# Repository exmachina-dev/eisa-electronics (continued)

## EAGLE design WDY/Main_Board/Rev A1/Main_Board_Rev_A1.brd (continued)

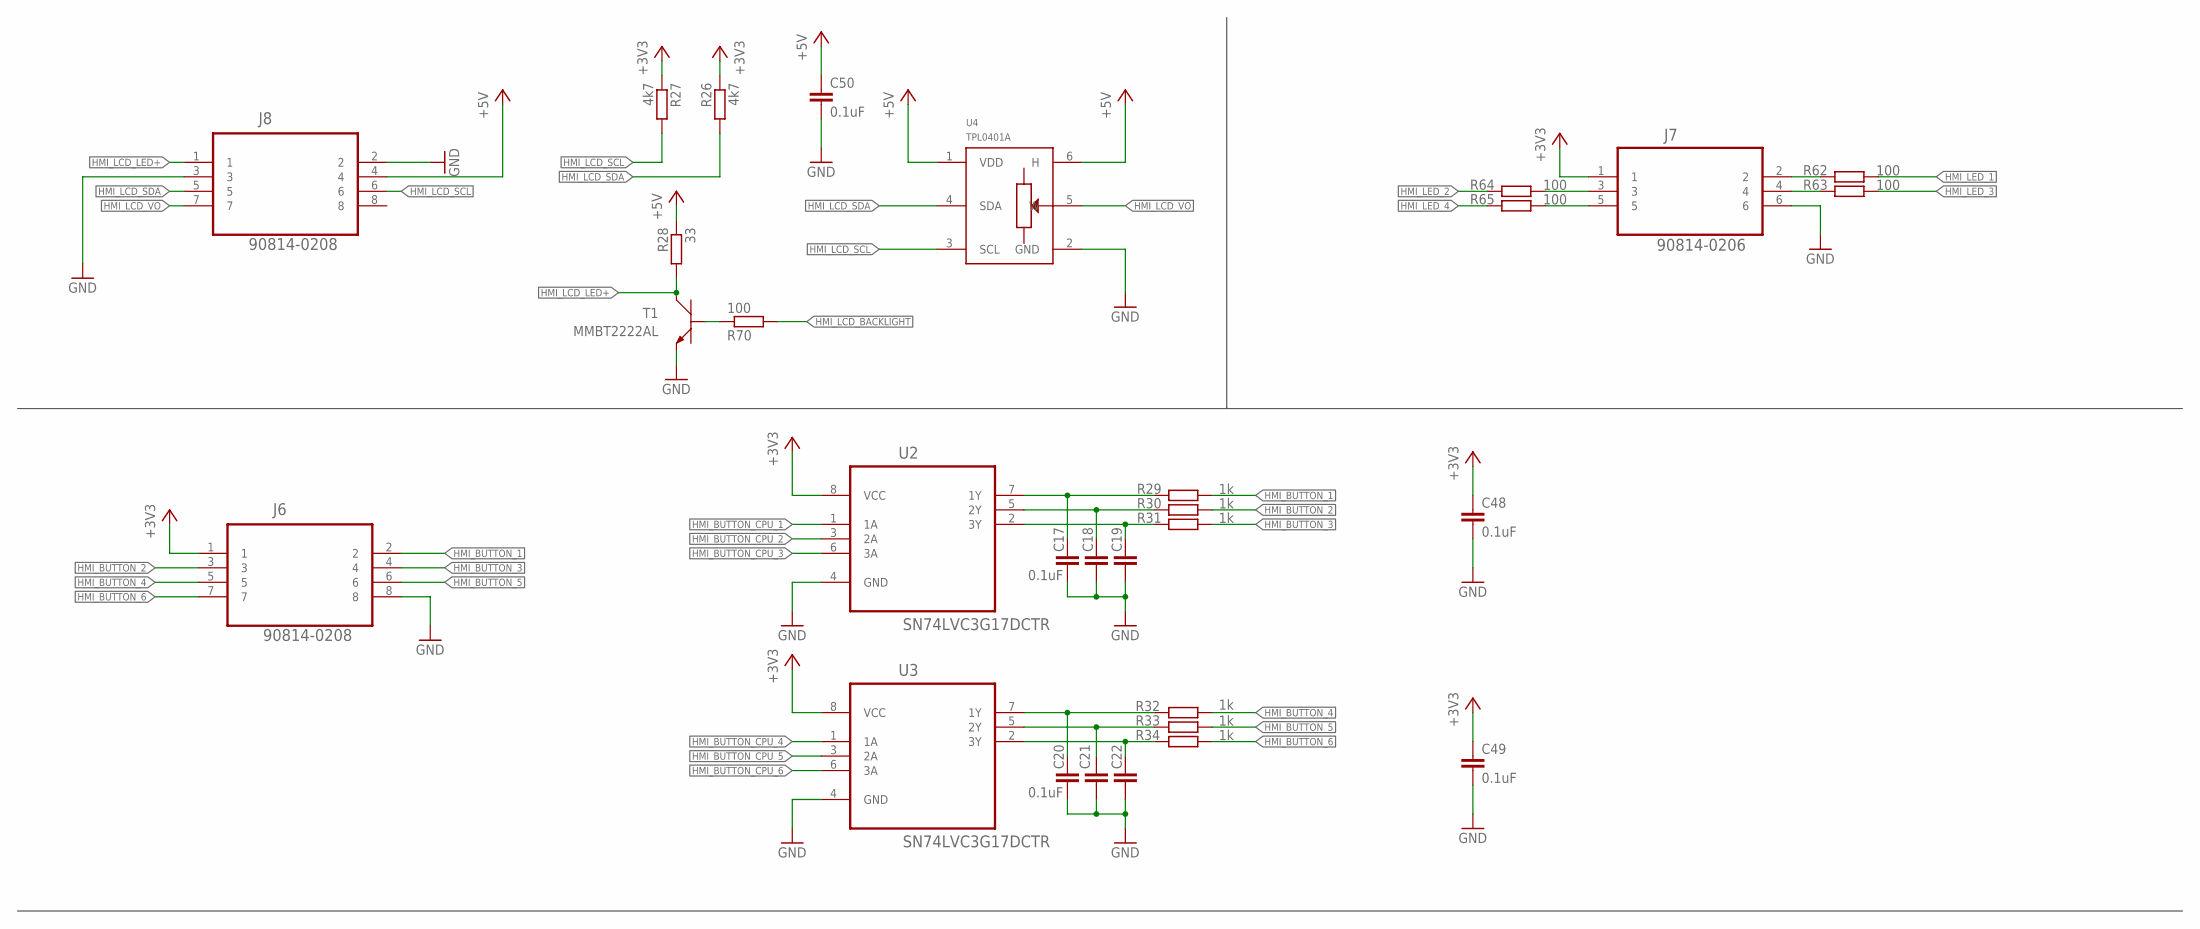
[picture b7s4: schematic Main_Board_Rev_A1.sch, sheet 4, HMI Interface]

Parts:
C17, C18, C19, C20, C21, C22, C48, C49, C50: 0.1uF; C0603
J6, J8: 90814-0208; MOLEX_90814-0208
J7: 90814-0206; MOLEX_90814-0206
R26, R27: 4k7; R0603
R28: 33; R0603
R29, R30, R31, R32, R33, R34: 1k; R0603
R62, R63, R64, R65, R70: 100; R0603
T1: MMBT2222AL; SOT−23
U2, U3: SN74LVC3G17DCTR; SOP65P400X130-8N
U4: TPL0401A; SC-70-DCK

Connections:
+3V3: C48.1, C49.1, J6.1, J7.1, R26.1, R27.1, U2.8 (VCC), U3.8 (VCC); also elsewhere on the board
+5V: C50.1, J8.4, R28.1, U4.1 (VDD), U4.6 (H); also elsewhere on the board
GND: C17.2, C18.2, C19.2, C20.2, C21.2, C22.2, C48.2, C49.2, C50.2, J6.8, J7.6, J8.2, J8.3, T1.2 (E), U2.4 (GND), U3.4 (GND), U4.2 (GND); also elsewhere on the board
HMI_BUTTON_1: J6.2, R29.1
HMI_BUTTON_2: J6.3, R30.1
HMI_BUTTON_3: J6.4, R31.1
HMI_BUTTON_4: J6.5, R32.1
HMI_BUTTON_5: J6.6, R33.1
HMI_BUTTON_6: J6.7, R34.1
HMI_BUTTON_CPU_1: U2.1 (1A); also elsewhere on the board
HMI_BUTTON_CPU_2: U2.3 (2A); also elsewhere on the board
HMI_BUTTON_CPU_3: U2.6 (3A); also elsewhere on the board
HMI_BUTTON_CPU_4: U3.1 (1A); also elsewhere on the board
HMI_BUTTON_CPU_5: U3.3 (2A); also elsewhere on the board
HMI_BUTTON_CPU_6: U3.6 (3A); also elsewhere on the board
HMI_LCD_BACKLIGHT: R70.2; also elsewhere on the board
HMI_LCD_LED+: J8.1, R28.2, T1.3 (C)
HMI_LCD_SCL: J8.6, R27.2, U4.3 (SCL); also elsewhere on the board
HMI_LCD_SDA: J8.5, R26.2, U4.4 (SDA); also elsewhere on the board
HMI_LCD_VO: J8.7, U4.5 (W)
HMI_LED_1: R62.1; also elsewhere on the board
HMI_LED_2: R64.2; also elsewhere on the board
HMI_LED_3: R63.1; also elsewhere on the board
HMI_LED_4: R65.2; also elsewhere on the board
unnamed: J7.3, R64.1
unnamed: J7.5, R65.1
unnamed: R70.1, T1.1 (B)
unnamed: C17.1, R29.2, U2.7 (1Y)
unnamed: C18.1, R30.2, U2.5 (2Y)
unnamed: C19.1, R31.2, U2.2 (3Y)
unnamed: C20.1, R32.2, U3.7 (1Y)
unnamed: C21.1, R33.2, U3.5 (2Y)
unnamed: C22.1, R34.2, U3.2 (3Y)
unnamed: J7.2, R62.2
unnamed: J7.4, R63.2

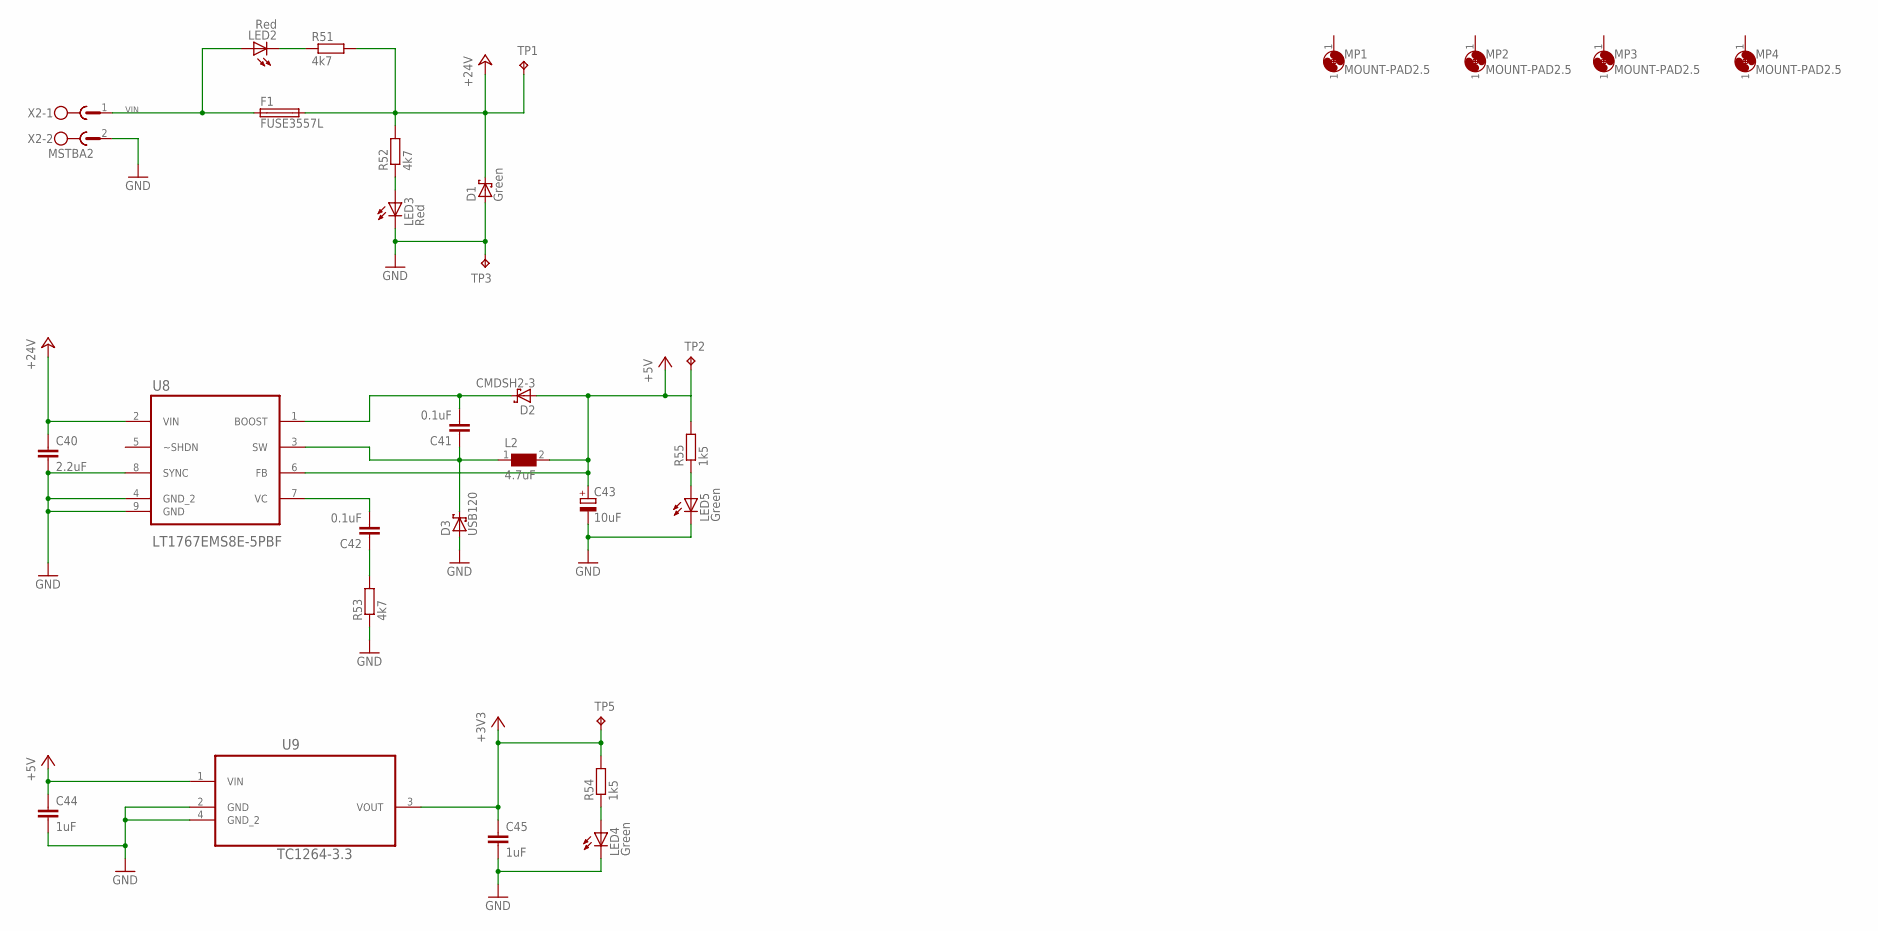
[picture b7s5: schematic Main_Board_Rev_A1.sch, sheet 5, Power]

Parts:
C40: 2.2uF; C0603
C41, C42: 0.1uF; C0603
C43: 10uF; CT3216
C44, C45: 1uF; C0603
D1: Green; SMB
D2: CMDSH2-3; SOD323-W
D3: USB120; DO216AA
F1: FUSE3557L; 3557-LITTLE
L2: 4.7uF; WE-PD_1030/1050
LED2, LED3: Red; CHIPLED_0603
LED4, LED5: Green; CHIP-LED0603; MPN OVS-0604
MP1, MP2, MP3, MP4: MOUNT-PAD2.5; P2.5
R51, R52, R53: 4k7; R0603
R54, R55: 1k5; R0603; MPN MCMR06X1501FTL
TP1, TP2, TP3, TP5: TPB1,27; B1,27
U8: LT1767EMS8E-5PBF; SOP65P490X110-9N
U9: TC1264-3.3; SOT230P700X180-4N
X2: MSTBA2

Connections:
+3V3: C45.1, R54.2, TP5.TP, U9.3 (VOUT); also elsewhere on the board
+5V: C43.+, C44.1, D2.A, L2.2, R55.2, TP2.TP, U8.6 (FB), U9.1 (VIN); also elsewhere on the board
+24V: C40.1, D1.C, F1.3 (2), F1.4 (2), R51.2, R52.2, TP1.TP, U8.2 (VIN); also elsewhere on the board
GND: C40.2, C43.-, C44.2, C45.2, D1.A, D3.A, LED3.C, LED4.C, LED5.C, R53.1, TP3.TP, U8.4 (GND_2), U8.8 (SYNC), U8.9 (GND), U9.2 (GND), U9.4 (GND_2), X2.2; also elsewhere on the board
unnamed: C41.2, D2.C, U8.1 (BOOST)
unnamed: LED3.A, R52.1
unnamed: LED2.C, R51.1
unnamed: C42.1, R53.2
unnamed: C42.2, U8.7 (VC)
unnamed: C41.1, D3.C, L2.1, U8.3 (SW)
unnamed: LED4.A, R54.1
unnamed: LED5.A, R55.1
VIN: F1.1, F1.2 (1), LED2.A, X2.1

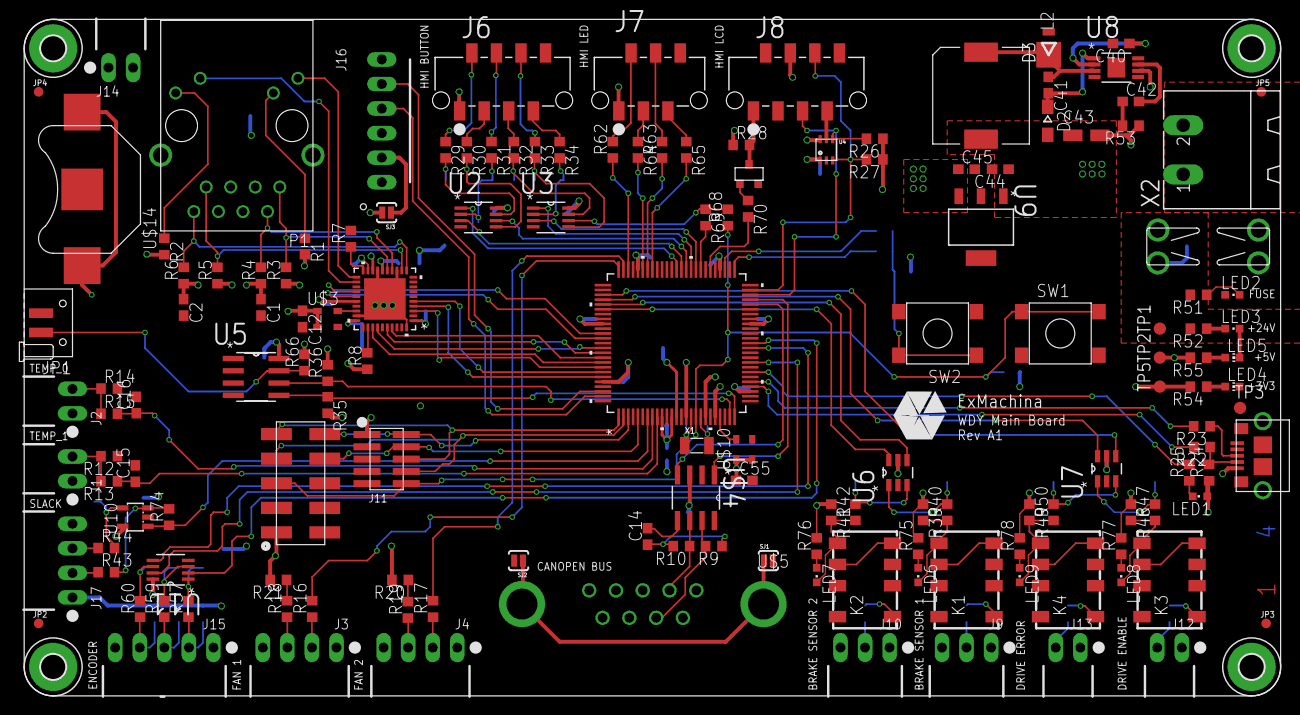
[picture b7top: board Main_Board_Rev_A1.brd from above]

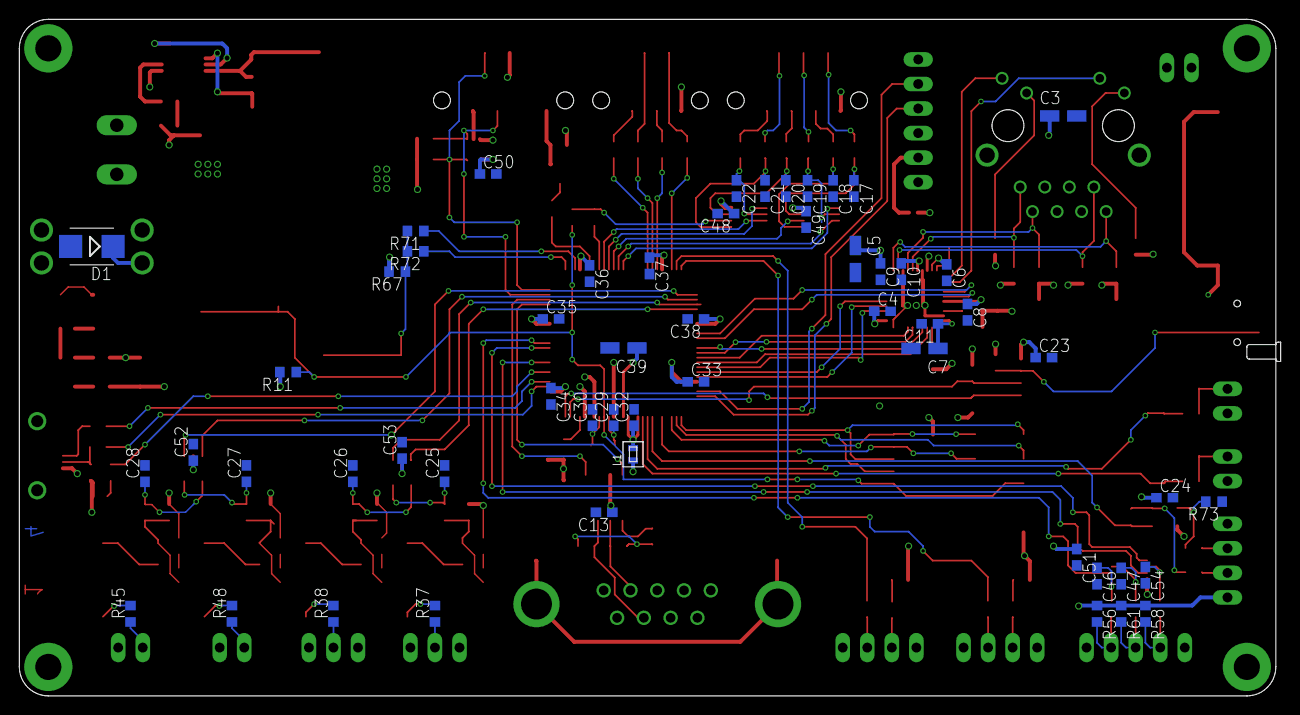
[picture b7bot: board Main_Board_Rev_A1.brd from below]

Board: 4 copper layers, 130.5 x 70.0 mm, 209 parts (55 on the bottom side), 154 nets.

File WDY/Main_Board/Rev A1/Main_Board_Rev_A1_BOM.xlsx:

|  |  | Project | WDY - Main Board
 |  |  | Author | AB
 |  |  | Date | 42709
 |  |  | Rev | A1
Qty | Value | Device | Package | Parts | Description
1 | Green | LEDCHIPLED_0603 | CHIPLED_0603 | LED1 | LED
1 |  | STPS3L40UF | SMB | D1
31 | 0.1uF | C-EUC0603 | C0603 | C17, C18, C19, C20, C21, C22, C23, C24, C25, C26, C27, C28, C32, C33, C34, C35,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 | CAPACITOR, European symbol
1 | 0603PS-103KLB | 0603PS | 603 | L1
4 | 0R | R-EU_R0603 | R0603 | R68, R69, R71, R72 | RESISTOR, European symbol
19 | 100 | R-EU_R0603 | R0603 | R17, R18, R19, R37, R38, R40, R42, R45, R47, R48, R50, R57, R59, R60, R62, R63,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 | RESISTOR, European symbol
10 | 100nF | C-EUC0603 | C0603 | C1, C2, C4, C6, C8, C9, C10, C11, C12, C13 | CAPACITOR, European symbol
2 | 10K | R-EU_R0603 | R0603 | R11, R67 | RESISTOR, European symbol
6 | 10k | R-EU_R0603 | R0603 | R12, R13, R14, R15, R20, R21 | RESISTOR, European symbol
4 | 10uF | CPOL-EUCT3216 | CT3216 | C5, C7, C39, C43 | POLARIZED CAPACITOR, European symbol
1 | 1241050-5 | 1241050-5 | 2.54/2X5 | J5
2 | 18pF | C-EUC0603 | C0603 | C29, C30 | CAPACITOR, European symbol
1 | 1K | R-EU_R0603 | R0603 | R16 | RESISTOR, European symbol
6 | 1k | R-EU_R0603 | R0603 | R29, R30, R31, R32, R33, R34 | RESISTOR, European symbol
2 | 1k2 | R-EU_R0603 | R0603 | R73, R74 | RESISTOR, European symbol
2 | 1k5 | R-EU_R0603 | R0603 | R24, R25 | RESISTOR, European symbol
2 | 1k5 | R-EU_R0603 | R0603 | R54, R55 | RESISTOR, European symbol
2 | 1k8 | R-EU_R0603 | R0603 | R43, R44 | RESISTOR, European symbol
2 | 1uF | C-EUC0603 | C0603 | C44, C45 | CAPACITOR, European symbol
1 | 2.2uF | C-EUC0603 | C0603 | C40 | CAPACITOR, European symbol
5 | 22-05-7028-02 | 22-05-7028-02 | 2007041 | J1, J2, J12, J13, J14 | CONNECTOR
2 | 22-05-7038-03 | 22-05-7038-03 | 2007069 | J9, J10 | CONNECTOR
3 | 22-05-7048-04 | 22-05-7048-04 | 2007100 | J3, J4, J17 | CONNECTOR
1 | 22-05-7058-05 | 22-05-7058-05 | 2007130 | J15 | CONNECTOR
1 | 22-27-2061-06 | 22-27-2061-06 | 1647397 | J16 | CONNECTOR
2 | 220 | R-EU_R0603 | R0603 | R1, R2 | RESISTOR, European symbol
1 | 3000 | 3000 | 3000 | U$14
3 | 33 | R-EU_R0603 | R0603 | R22, R23, R28 | RESISTOR, European symbol
2 | 4.7uF | C-EUC0603 | C0603 | C15, C16 | CAPACITOR, European symbol
1 | 4.7uF | CPOL-EUCT3216 | CT3216 | C3 | POLARIZED CAPACITOR, European symbol
1 | 4.7uF | WE-PD-7447713047_1030/1050 | WE-PD_1030/1050 | L2 | SMD-Shielded Power Inductors WE-PD
1 | 4700pF | C-EUC0603 | C0603 | C14 | CAPACITOR, European symbol
4 | 49.9 | R-EU_R0603 | R0603 | R3, R4, R5, R6 | RESISTOR, European symbol
1 | 4K7 | R-EU_R0603 | R0603 | R8 | RESISTOR, European symbol
1 | 4K87 | R-EU_R0603 | R0603 | R7 | RESISTOR, European symbol
15 | 4k7 | R-EU_R0603 | R0603 | R26, R27, R35, R36, R39, R41, R46, R49, R51, R52, R53, R56, R58, R61, R66 | RESISTOR, European symbol
1 | 5504F1-09S-02A-03 | 5504F1-09S-02A-03 | 5504F1-09S-02A | U$5 | D-Sub 9pts, Righ-angle, solder
2 | 60 | R-EU_R0603 | R0603 | R9, R10 | RESISTOR, European symbol
1 | 90814-0206 | 90814-0206 | MOLEX_90814-0206 | J7 | CONN HEADER 06 POS 1.27MM SMD TIN
2 | 90814-0208 | 90814-0208 | MOLEX_90814-0208 | J6, J8 | CONN HEADER 8POS 1.27MM SMD TIN
1 | ASE-12 | ASE | ASE | U$10 | 3.3Vdc CMOS SMD CRYSTAL CLOCK OSCILLATOR
1 | ASE_50 | ASE | ASE | U$3 | 3.3Vdc CMOS SMD CRYSTAL CLOCK OSCILLATOR
1 | AT24C512C-SSHM-B | AT24C512C-SSHM-B | SOIC127P600X175-8N | U5 | SERIAL EEPROM IC Memory Size:512Kbit,8-SOIC
2 | B3FS-1015 | B3FS-1015 | B3FS | SW1, SW2 | Surface-mounting Switches Ideal for
1 | BC-2-P | BC-2-P | BC-2-P | JP1
1 | CMDSH2-3 | CMDSH2-3 | SOD323-W | D2
1 | DP83848JSQ/NOPB | DP83848JSQ/NOPB | SQA40B | U$2
1 | FC-135 | FC-135 | FC-135 | X1 | 32.768kHz ±20ppm Crystal 12.5pF 70 kOhm -40°C ~ 85°C Surface Mount 2-SMD
1 | FTSH-105-01-L-DV | FTSH-105-01-L-DV | FTSH-105-01-L-DV | J11
1 | FUSE3557L | FUSE3557L | 3557-LITTLE | F1 | Fuse
4 | G6K-2G-Y | G6K-2G-Y | G6K-2G-Y | K1, K2, K3, K4 | Low Signal Relay
2 | Green | LEDCHIP-LED0603 | CHIP-LED0603 | LED4, LED5 | LED
1 | LPC1768FBD100 | LPC1768FBD100 | SOT407-1 | U1
1 | LT1767EMS8E-5PBF | LT1767EMS8E-5PBF | SOP65P490X110-9N | U8 | Step-Down Switching Regulators
1 | MCP2561-E/SN | MCP2561-E/SN | SOIC127P600X175-8N | U$4 | High-Speed CAN Transceiver
1 | MMBT2222AL | MMBT2222AL | SOT-23 | T1 | General Purpose Transistors
1 | MSTBA2 | MSTBA2 | MSTBA2 | X2 | PHOENIX
1 | RB1-125BAG1A | RB1-125BAG1A | WIZNET_RB1-125BAG1A | P1 | Accessory RJ-45 With Transformer Connector - UDE
2 | Red | LEDCHIPLED_0603 | CHIPLED_0603 | LED2, LED3 | LED
2 | SN74LVC2G17DBVR | SN74LVC2G17DBVR | SOT95P280X145-6N | U6, U7 | DUAL SCHMITT-TRIGGER BUFFER
3 | SN74LVC3G17DCTR | SN74LVC3G17DCTR | SOP65P400X130-8N | U2, U3, U11 | TRIPLE SCHMITT-TRIGGER BUFFER
1 | TC1264-3.3 | TC1264-3.3 | SOT230P700X180-4N | U9 | IC, 8
1 | TLV313 | TLV313 | SOT23-DBV | U10
1 | TPL0401A | TPL0401A | SC-70-DCK | U4
1 | USB120 | USB120 | DO216AA | D3
1 | USB3075-30-A | USB3075-30-A | USB_MICROB_SMT | U$6

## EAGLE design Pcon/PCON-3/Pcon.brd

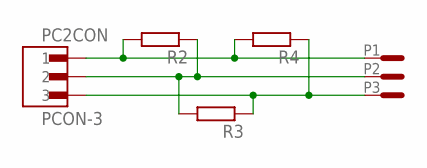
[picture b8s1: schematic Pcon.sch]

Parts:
PC2: PCON-3
R2, R3, R4: R-EU_R0603; R0603

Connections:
unnamed: PC2.3, PC2.P3, R3.1, R4.1
unnamed: PC2.2, PC2.P2, R2.1, R3.2
unnamed: PC2.1, PC2.P1, R2.2, R4.2

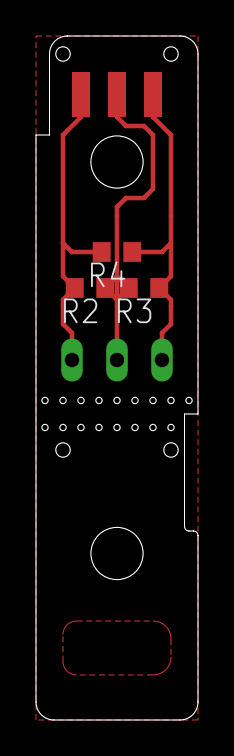
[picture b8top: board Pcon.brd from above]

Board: 2 copper layers, 9.0 x 38.0 mm, 4 parts (0 on the bottom side), 3 nets.

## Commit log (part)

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2015-12-20 Updated exmachina.lbr and holes.lbr
    Moved logo and text to tPlace
    Restrict circles were too big.
2015-12-20 Added GERBER RS274X files for Varmo - Rev A1
2015-12-23 Added GERBER files for ArmazCape Rev B3
2015-12-23 Added GERBER files for ArmazConnect - Rev B3
2015-12-23 Update Armaz schematic and board, generate GERBER file
2016-02-17 Add directory to simu and add simulation of the contrast value
2016-03-03 Add pulse library with the H1102FNL chip
2016-03-03 Create schematic for rev A2 of Armaz ethernet, Addd power suplly + ethernet connector
2016-03-03 Add SMAJ33A to diode library
2016-03-03 Add Ethernet chip with is power connection
2016-03-04 Add power filtering of the ehernet chip and the crystal
2016-03-07 Add EEPROM and SPI connector and connector between the two board
2016-03-08 Add +1V8 symbol to supply1.lbr, update the schematic and the board
2016-03-09 Place all connectors and route all the front board
2016-03-09 Replace 1x6 to 1x8 connector Add leds for ethernet 1 and 2 Change value of led resistor
2016-03-09 Update the board with the update schematic
2016-03-10 Update board and change NC to DNI
2016-03-11 Board all route
2016-03-14 Update Armaz Ethernet board
2016-03-15 Route KSZ8851
2016-03-16 Route the KSZ8851 board
2016-03-16 Fix wire angle on the board
2016-03-16 Fix angle wire on the board
2016-03-17 Generate gerber file
2016-03-17 Add Exmachina logo and CC
2016-03-17 3D export
2016-03-17 Update 3D export
2016-03-17 Generate new IDF of the board update
2016-03-21 Add AT93C46EN-SH-B component to Atmel library
2016-03-21 Panel the board
2016-03-22 Added paddle ground to KSZ8851SNL
2016-03-25 Add 1N4148W to lib
2016-03-25 Turn JP2 Add res to L3 Add reset circuit Add rev to the silkscreen Add Keepout near the transfo
2016-03-25 Add restric near Magjack
2016-03-29 Update the route of the board and the schematic
2016-03-29 Add file cam for PCB Way
2016-03-29 New IDF
2016-03-30 Generate Gerber
2016-03-30 Update gerber
2016-03-30 Add fiducial to the board
2016-03-30 Update the gerber
2016-04-01 Create lineartechnology library with LT1813CS8
2016-04-01 Update symbol of NPN
2016-04-01 Update symbol of AOP without power
2016-04-13 Update ArmazEthernet board
2016-04-13 Update the visio document for the Varmo Stand
2016-04-15 Add ressource to M20DX256
2016-04-15 Create GlobalConnectorTechnology library Add UBS Micro B to the library
2016-04-15 Add JTAG/SWD header
2016-04-15 Place the component on the board
2016-04-15 Create library for custom connector Add 21 pins connector to it
2016-04-18 Connect all the ports to the connectors
2016-04-18 Add reset to the board and the schematic
2016-04-18 Change the prefix of the ABS07 to Y
2016-04-18 Add 32Mhz oscillator
2016-04-18 change connector J2 and J3 add LED on PTD4
2016-04-19 route J3
2016-04-19 Route J1
2016-04-19 Route the power supply +5V
2016-04-19 Add test pad and curve the corner of the board
2016-04-19 Add name of the board, CC, and logo of exmachina
2016-04-19 Deleted C4 and C5 Renaming C6 to C4
2016-04-19 Generate IDF
2016-04-20 update schematic: Put +5V on J2 pin 20 and GND on J3 pin 20
2016-04-20 Sum up thje pin out of the mk20dx proto board
2016-04-20 Add PCA9665D to the board for managing the LCD Bus control
2016-04-20 Add the connector symbol for MC41605 to the library Midas
2016-04-20 Add LCD connector to the board
2016-04-20 Add connector for the LCD board
2016-04-20 Add the reference to the joystick to the Varmo stand visio
2016-04-21 Route the neutrik panel
2016-04-21 Update the siwe of the via of the connector of MC41605A
2016-04-21 Add 22-05-7028 connector to the library
2016-04-21 Update the board with the new footprint for the USB Micro type B
2016-04-21 Update the schematic with the correction of Varmo rev A1
2016-04-22 Route the power on the LCD Board
2016-04-22 Fux bug on LT1813CS8 and MMBT2222AL tplace
2016-04-22 Change LED connector to 3 pts
2016-04-25 Add TC1262 5.5V and 3V3 to the microship library
2016-04-25 Update the visio of varmo stand
2016-04-25 Deleted the tkeepout of the footprint sot230
2016-04-25 Create Rev A3 of ArmazEthernet
2016-04-25 Change the 3V3 and 1V8 circuit and place the component
2016-04-25 Put the LED of Neutrik connectors on pull-down
2016-04-27 update the route of the board
2016-04-27 Choose connector for joystick
2016-04-27 Place the connector of the thumbwheels and joystick on the board
2016-04-28 Resized NC BY-NC-SA logo
2016-04-28 Change CC-BY-NC-SA logo on the board ArmazEthernet Rev A3
2016-04-28 Change CC-BY-NC-SA logo on the board Varmo Rev A2
2016-04-28 Add joystick direction to RKJT1F
2016-04-28 Add joystick to the board varmo rev a2
2016-04-29 route the decoupling capacitors of the kz8995
2016-04-29 Move C46 and c12
2016-04-29 Place the component and route the joystick panel
2016-05-02 Route the LCD panel with the good placement for the four LED Route the joystick panel with the mounting hole
2016-05-02 Export the visio into PDF
2016-05-02 Move the link between joystick panel and LCD screen
2016-05-02 replace 20 pins connector to 21 pins connector
2016-05-02 route all the airwire
2016-05-02 Update the reference of the components on the board
2016-05-02 Generate gerber files
2016-05-02 Generrate gerber and archive the gerber files
2016-05-03 Move the name on the board and generate the new gerber
2016-05-03 Replace the jtag connector
2016-05-03 Generate new gerber
2016-05-04 Add the clocks to the arm
2016-05-04 Add the +3V3 LDO and change the position of the connector
2016-05-09 Invert the GND plan and the power 3V3 plan and space the Ethernet signal to have a GND plan between two Ethernet signal
2016-05-09 Finalize to reroute all the board
2016-05-09 Correctec the drc errors
2016-05-09 add option spin to exmachina logo
2016-05-09 add serigraphy for the test pad
2016-05-09 Replace pad by SMT
2016-05-10 update visio of varmo stand
2016-05-10 Reroute the joystick board
2016-05-10 Rename Varmo LED to lamp LED and add a resitor on input of the transistor
2016-05-10 Rename the board
2016-05-10 Rename the board to LedLamp
2016-05-10 add name on the pin of the jtag connector
2016-05-10 Rename gerber eurocircuit path and generate gerber for pcb way
2016-05-10 archive gerber PCB way
2016-05-11 Update the mechanical layer with the diameter of the wheels led
2016-05-11 Add connector molex 5 points to the lib
2016-05-11 Route the connector jogwheel
2016-05-11 Route the joystick connector
2016-05-11 Add encoder E20A serie to the librarie
2016-05-12 Routing the +3V3 and the +5V/1 power
2016-05-12 Place the logo and the CC on each board
2016-05-12 Add X097 serie footprint to the pot libraries
2016-05-12 Panelize the board
2016-05-20 Add eagles shortcut
2016-05-20 Add HCPL0201 to optocoupler librarie
2016-05-20 Replace the HCPL0601 with the HCPL0201 optocoupler
2016-05-20 Generate and zip Gerber files
2016-05-20 Regenerate gerber files
2016-05-21 Panelized board. Fixed broken trace. Regenerated GERBER files.
2016-05-23 Document encoder sheet
2016-05-23 Rename the name on the board
2016-05-23 Rename Jogwheel folder to JOGWE
2016-05-24 Generate BOm of Varmo - Rev A2
2016-05-31 Final changes before prod
    Resized board
    Better placement (minor changes)
2016-05-31 Added GERBER files for ArmazEthernet - Rev A3
2016-06-03 Create package of PCA9670
2016-06-03 Add PCA9670 to the schematic
2016-06-06 Correct the footprint of LT1813
2016-06-06 Update the LT1813 devide
2016-06-06 Modify the encoder with push button symbole
2016-06-06 Update the name of the EC20A and the RKJXT1F device
2016-06-06 Add Dario rev A2
2016-06-06 Enlarge the board to have a multiple of 0.1 inch
2016-06-06 Rename the name on the board and add the name on some pin of JTAG connector
2016-06-07 ArmazCape Rev B4
    Ported changes from KSZ8851 to ArmazCape Rev B4
    Reorganized layout of optocouplers
    Added 2 ESW (5-6)
    Added 3 Outs (0-2)
    UART4 routed to EXP0
2016-06-07 ArmazCape - Rev B4: Reorganized schematics layout
2016-06-09 Add TLP0401A to the schematic and route the board
2016-06-27 Deleted wrong trace
2016-07-01 Update the technologie of the screen
2016-07-01 Deleted the edge of the board and generate the gerber files
2016-07-18 IDF varmo screen
2016-08-17 Fix NC3MAAV package
2016-08-17 Update attributes in ArmazEthernet - Rev A3
2016-08-18 [VarmoEmergencyStop] Colorized board and schematics
2016-08-18 Update WKs scripts
    * Add color for schematics
    * Add menu icon to schematics
2016-08-18 Add ArmazConnect - Rev B4
    * Remove DMX section (May be implemented on another board)
    * Add PicoFlex connector with UART4, power, ESW5-6 and OUT1-2
    * Move status leds to the upper-right
    * Move 26 pin commector to the back
    * Fix missing current limiting resistor for UART5
2016-10-04 Fix #6: Create Varmo Rev A3 Ajust LED Position
2016-10-05 REplace the old version of LCD Screen by the new one
2016-10-05 Add PCA9671D part to NXP library
2016-10-05 Update pin mane of PCA9671D
2016-10-13 Fix #8: Add filter and shmitt trigger to encoder inputs.
2016-11-24 Change relay to G6K Place components on the board
2016-11-25 Power polygon on the board
2016-11-28 HMI_Board : Add the revision on the folder
2016-11-28 Route the signal of USB, CAN, ETH, Relay, LED, Button, ADC
2016-11-30 Finishing routing and adding FTDI connector
2016-11-30 Rerouting the 2 airwiries
2016-12-01 Fix : HMI_BUTTON_CPU_6 configuration is misleading
2016-12-01 Fix : Ethernet filters connection misleading
2016-12-01 Fix : Ethernet clock (@1.C8): TRI pin to VDD or NC to enable oscillator
2016-12-01 Fix : MCU clock (@2.C1): TRI pin to VDD or NC to enable oscillator
2016-12-01 Fix : Inverted input / output on all SN74LVC (U6 and U7)
2016-12-01 Add MSTBA2 To con-phoenix-508 lib
2016-12-01 Update connector packages in libraries
2016-12-01 Put J16 on top layer
2016-12-05 Rename board to Main_Board_Rev_A1
2016-12-05 Add ASE to crystal library
2016-12-05 Update libraries
2016-12-05 Add name and fiducial
2016-12-05 Add LED value
2016-12-05 Add value on LED
2016-12-05 Generate the BOM of the HMI Board
2016-12-06 Add power balance of the Main Board and update the BOM
2016-12-06 Add power balance of HMI Board
2016-12-06 Add power balance of Armaz board
2016-12-06 Add PCON 2-P, 3 and 3-P connector and BCON to exmachina.lbr
2016-12-06 Modified packages in libraries
    * Simplified DB9 connector in con-multicomp.lbr
    * Redesigned fuse package in fuse2.lbr
    * Update packages in Main_Board_Rev_A1
2016-12-06 Add PCON connectors project and its GERBER files
2016-12-06 Update PCON GERBER files
2016-12-06 Change LED position and generate gerber
2016-12-06 Genrate zip of the gerber
2016-12-06 Add individual files for PCON 2 and 3
2016-12-08 Update BOM of Main Board
2016-12-21 Update components names and placement and connect VREFN to GND.
2017-01-04 Change layer top silkscreen
2017-01-04 Add Com_Board schematic
2017-01-05 Add prefix X to ASE device
2017-01-05 Add schematic and route the Ethernet board
2017-01-05 Re-size the board
2017-01-05 Rotate 90 the board
2017-01-06 All 4mm fillet to the Ethernet Board
2017-01-06 Add 4mm fillet
2017-01-06 Remove eagle-resources files
2017-01-06 Add DESCRIPTION files and update README.md
2017-09-13 Retoute UART isolation
2017-09-13 Edit DESCRIPTION file
2017-09-13 Update XLR3F and XLR5F silkscreen.
2017-09-25 Generate MDP files
2017-09-28 Add new board ArmazConnectLite for ONL
2017-09-28 Add board dimension
2017-10-03 generate gerber and MDP files
2017-10-04 Add ArmazRelay board
2017-10-06 Add power connector and NC output
2017-10-09 Rename 'ArmazRelay - RevA1' to 'ArmazRelay - Rev A1'
2017-11-16 Update relay package and add polarity on relay coil
2017-12-14 Add ArmazCape - Rev B4 - MDP files
